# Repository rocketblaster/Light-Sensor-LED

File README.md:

# Light Sensor LED

This circuit contained a LDR or photo cell. When the photo resistor detects light the 555 timer turns on and the LED turns on as a result. When it is covered or it is dark, the LED turns off.

## Features

- The board contains a light depedent resistor (LDR) or a photo resistor. 
- It senses how much light is coming and proceeds to activate the 555 timer as it is connected to pin 8, VCC of the 555 timer.
- Potentiometer adjusts the light sensitivity.
  
## Schematic

## PCB

## BOM

| Designator | Value |
| ---------- | ----- |
| R1         | 10K   |
| R2         | 22k   |
| R3         | 4.7k   |
| R4         | LDR   |
| R5         | 330   |
| R6         | 330   |
| C1         | 0.1uF |
| C2         | 0.01uF |
| U1         | NE555 |
| RV1         | 100k |
| D1         | LED |
| D2         | LED |

## Assembly / Usage

Best to assemble smaller parts first. Resistor, then capacitator, LEDs, and potentiometer. I would do the USB connector port last. Since I only put in the designator values, R1 is 10k, R2 is 22k, R3 is 4.7k, R3 is the LDR, R5 and R6 are 330 ohm resistor.
For capacitor, C1 is 0.1u and C2 is 0.01u, and LED can be any color but red would be better to make the bird evil.

The LDR does not need to be soldered in flush mostly because the shadows from other components make it go to one state sometimes. Shouldn't be that much of an issue though.

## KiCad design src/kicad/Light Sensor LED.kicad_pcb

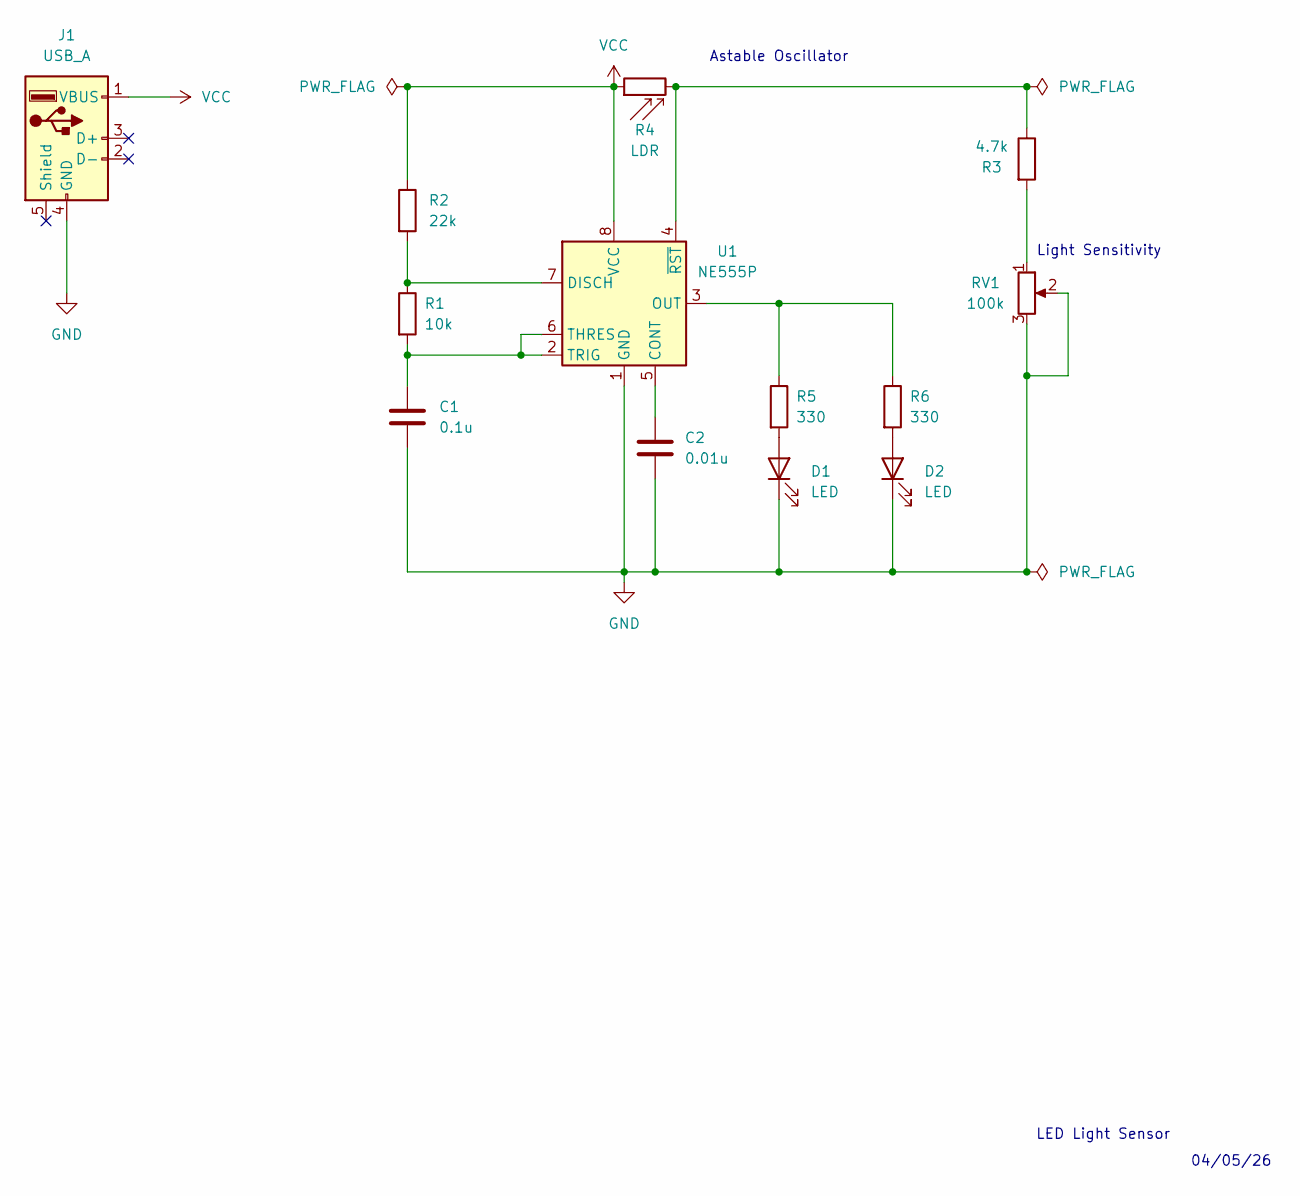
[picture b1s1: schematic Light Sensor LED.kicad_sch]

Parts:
C1: 0.1u; C_Disc_D8.0mm_W5.0mm_P5.00mm
C2: 0.01u; C_Disc_D8.0mm_W5.0mm_P5.00mm
D1, D2: LED; LED_D5.0mm
J1: USB_A; USB_A_Molex_67643_Horizontal
R1: 10k; R_Axial_DIN0204_L3.6mm_D1.6mm_P7.62mm_Horizontal
R2: 22k; R_Axial_DIN0204_L3.6mm_D1.6mm_P7.62mm_Horizontal
R3: 4.7k; R_Axial_DIN0204_L3.6mm_D1.6mm_P7.62mm_Horizontal
R4: LDR; R_LDR_4.9x4.2mm_P2.54mm_Vertical
R5, R6: 330; R_Axial_DIN0204_L3.6mm_D1.6mm_P7.62mm_Horizontal
RV1: 100k; Potentiometer_Bourns_3386P_Vertical
U1: NE555P; DIP-8_W7.62mm

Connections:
GND: C1.2, C2.2, D1.1 (K), D2.1 (K), J1.4 (GND), RV1.2, RV1.3, U1.1 (GND)
unnamed: D1.2 (A), R5.2
unnamed: D2.2 (A), R6.2
unnamed: R3.2, RV1.1
unnamed: C2.1, U1.5 (CONT)
unnamed: R1.1, R2.2, U1.7 (DISCH)
unnamed: R5.1, R6.1, U1.3 (OUT)
unnamed: C1.1, R1.2, U1.2 (TRIG), U1.6 (THRES)
unnamed: R3.1, R4.2, U1.4 (~RST)
VCC: J1.1 (VBUS), R2.1, R4.1, U1.8 (VCC)

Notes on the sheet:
Light Sensitivity
04/05/26
LED Light Sensor
Astable Oscillator

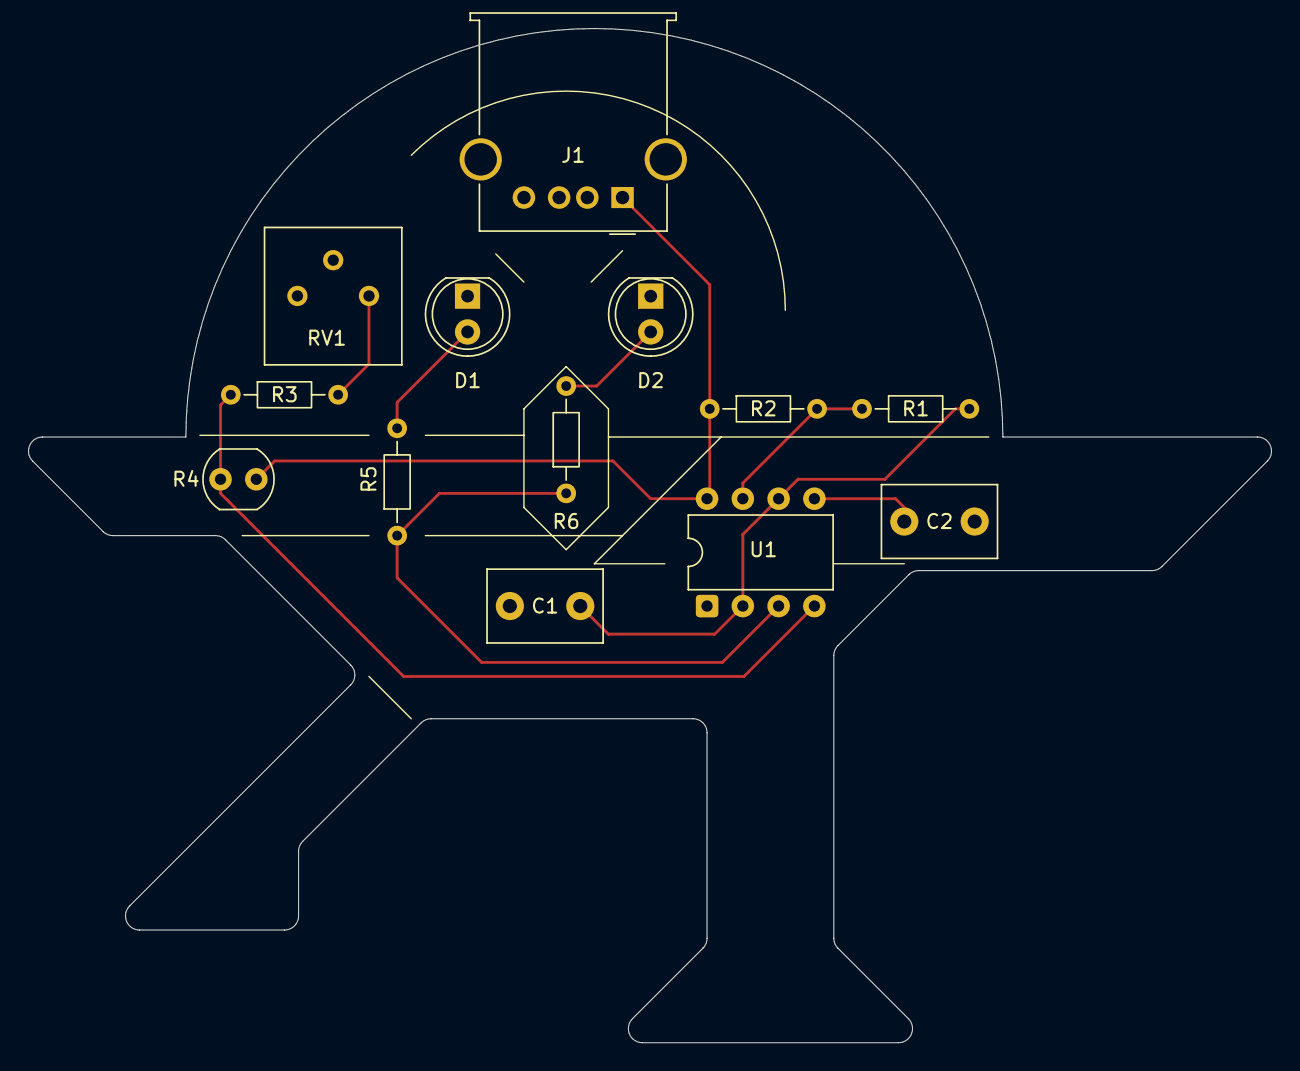
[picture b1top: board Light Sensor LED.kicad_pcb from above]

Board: 2 copper layers, 88.2 x 72.0 mm, 13 parts (0 on the bottom side), 10 nets.

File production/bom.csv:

Designator,Footprint,Quantity,Value,LCSC Part #
C1,C_Disc_D8.0mm_W5.0mm_P5.00mm,1,0.1u,
C2,C_Disc_D8.0mm_W5.0mm_P5.00mm,1,0.01u,
"D1, D2",LED_D5.0mm,2,LED,
J1,USB_A_Molex_67643_Horizontal,1,USB_A,
R1,R_Axial_DIN0204_L3.6mm_D1.6mm_P7.62mm_Horizontal,1,10k,
R2,R_Axial_DIN0204_L3.6mm_D1.6mm_P7.62mm_Horizontal,1,22k,
R3,R_Axial_DIN0204_L3.6mm_D1.6mm_P7.62mm_Horizontal,1,4.7k,
R4,R_LDR_4.9x4.2mm_P2.54mm_Vertical,1,LDR,
"R5, R6",R_Axial_DIN0204_L3.6mm_D1.6mm_P7.62mm_Horizontal,2,330,
RV1,Potentiometer_Bourns_3386P_Vertical,1,100k,
U1,DIP-8_W7.62mm,1,NE555P,

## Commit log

2026-04-05 Upload Journal.MD
2026-04-05 Upload README.MD
2026-04-05 Upload LightDetector.gif
2026-04-05 Move LightDetector.gif to attachments
2026-04-06 Upload image1.png
2026-04-06 Upload image2.png
2026-04-06 Upload image3.png
2026-04-06 Upload image4.png
2026-04-06 Upload image5.png
2026-04-06 Upload image6.png
2026-04-07 Upload image7.png
2026-04-07 Upload image8.png
2026-04-07 Upload image9.png
2026-04-07 Upload image10.png
2026-04-07 Upload image11.png
2026-04-09 Upload Image
2026-04-09 Update Journal
2026-04-10 Upload image14.png
2026-04-10 Upload image15.png
2026-04-10 Upload image16.png
2026-04-10 Upload image17.png
2026-04-11 Update Overall Project
2026-04-11 Update Project with Hero Image
2026-04-11 Update Hero Image
2026-04-17 Finish Project with Feedback
2026-04-17 Revised Project
